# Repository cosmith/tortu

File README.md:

Tortu is an open source storyteller and music player for kids.

It's also a work in progress :)

Current state:

# Todo

## App
- [ ] interface to be able to quickly add a file from youtube/spotify
- [ ] use dall-e or equivalent api to generate cover pictures
- [ ] use any llm to generate a short name for the story
- [ ] use elevenlabs or equivalent api to generate name

## Tortu
- [x] read files from sd card
- [x] play sound
- [x] display something on the screen
- [ ] finalize design
- [x] implement music / story switch
- [x] add volume control
- [x] add 3.5mm jack output

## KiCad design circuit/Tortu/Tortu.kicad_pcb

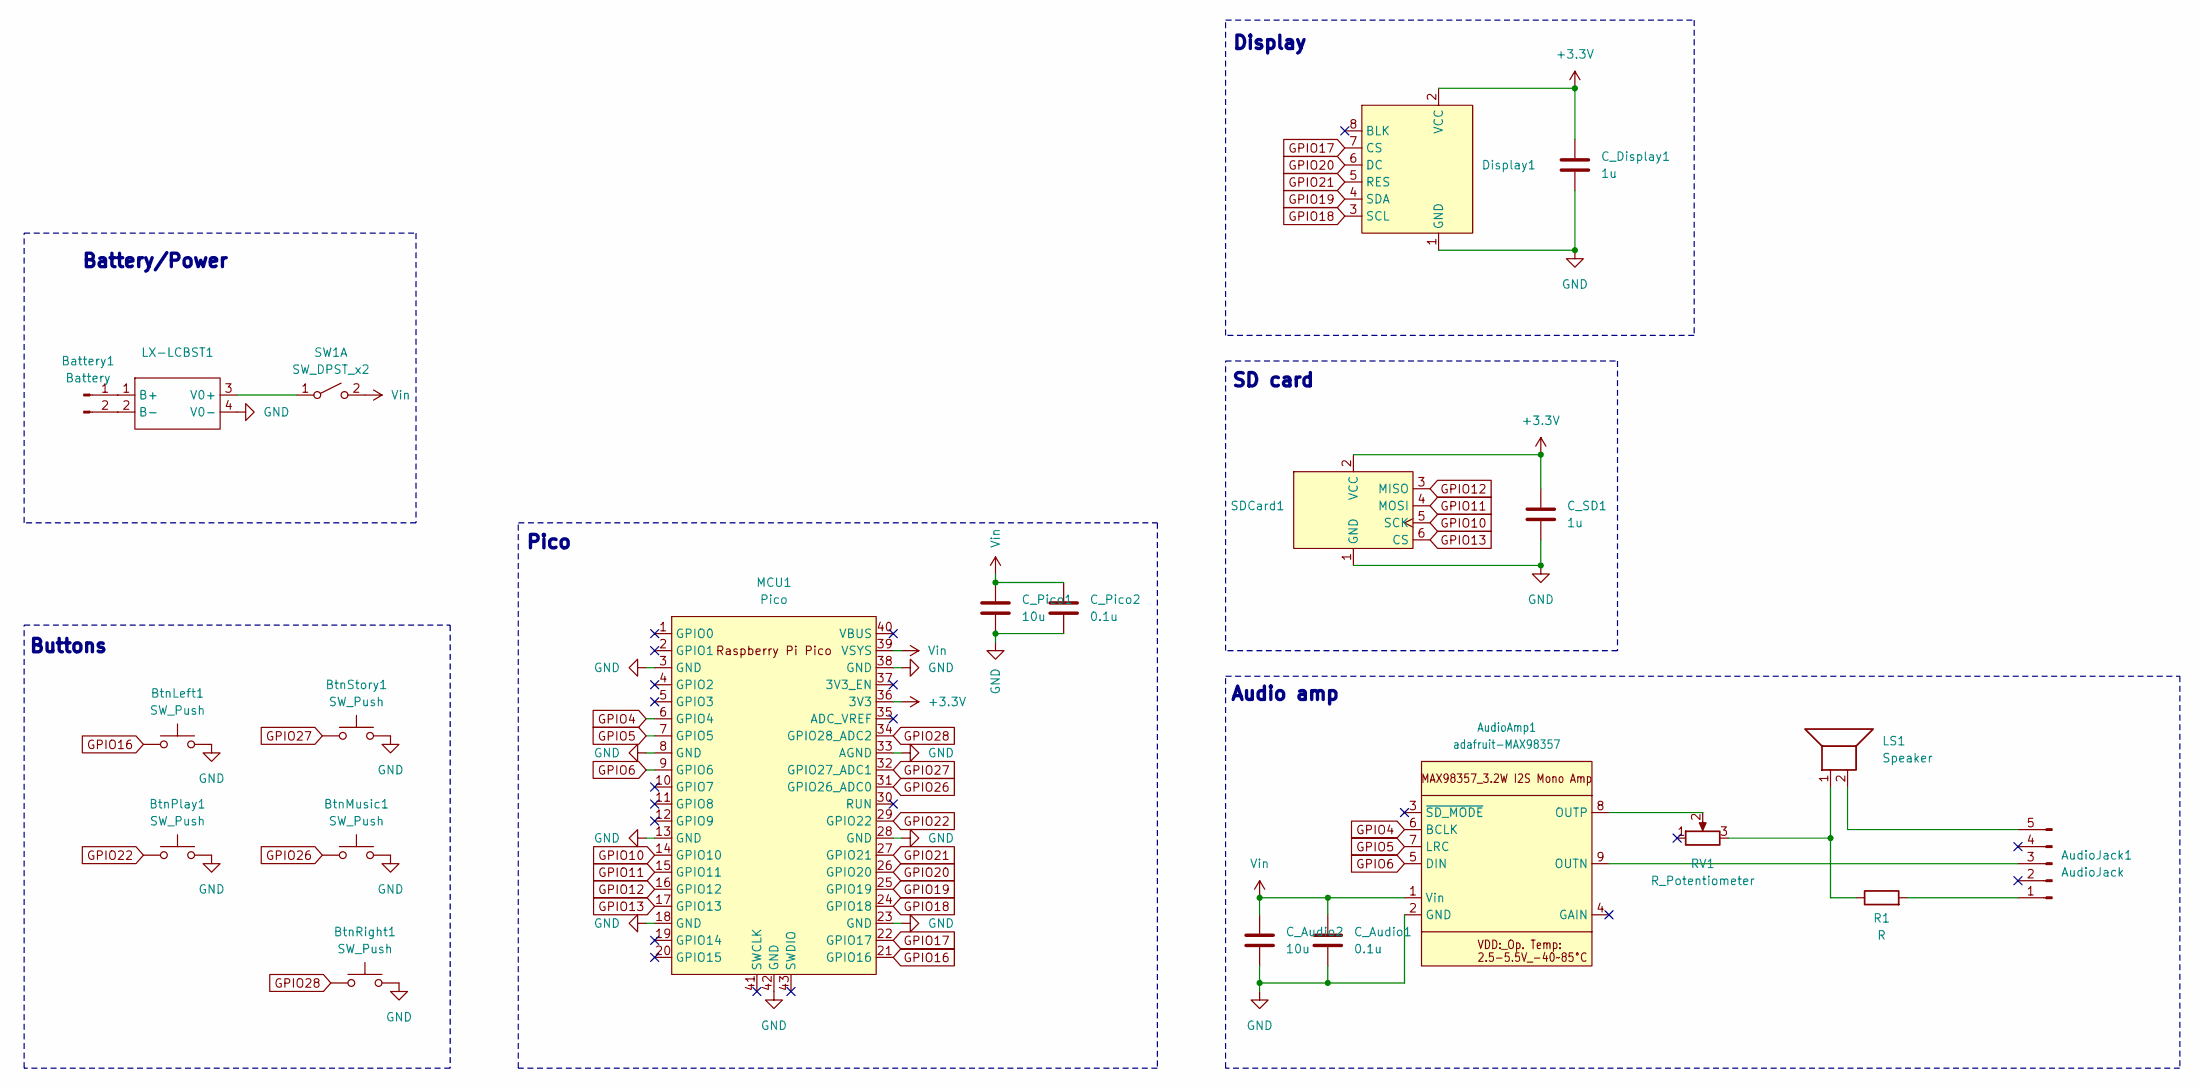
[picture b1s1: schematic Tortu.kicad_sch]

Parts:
AudioAmp1: adafruit-MAX98357
AudioJack1: AudioJack; PinHeader_1x05_P2.54mm_Vertical
Battery1: Battery; PinHeader_1x02_P2.54mm_Vertical
BtnLeft1: SW_Push; SW_PUSH_6mm_H5mm
BtnMusic1: SW_Push; SW_PUSH_6mm_H5mm
BtnPlay1: SW_Push; SW_PUSH_6mm_H5mm
BtnRight1: SW_Push; SW_PUSH_6mm_H5mm
BtnStory1: SW_Push; SW_PUSH_6mm_H5mm
C_Audio1: 0.1u; C_Disc_D3.8mm_W2.6mm_P2.50mm
C_Audio2: 10u; C_Disc_D3.8mm_W2.6mm_P2.50mm
C_Display1: 1u; C_Disc_D3.8mm_W2.6mm_P2.50mm
C_Pico1: 10u; C_Disc_D3.8mm_W2.6mm_P2.50mm
C_Pico2: 0.1u; C_Disc_D3.8mm_W2.6mm_P2.50mm
C_SD1: 1u; C_Disc_D3.8mm_W2.6mm_P2.50mm
Display1: Display_135x240IPS
LS1: Speaker; PinHeader_1x02_P2.54mm_Vertical
LX-LCBST1: BatteryCharginModule_LX-LCBST
MCU1: Pico; RPi_Pico_SMD_TH
R1: R; R_Axial_DIN0207_L6.3mm_D2.5mm_P10.16mm_Horizontal
RV1: R_Potentiometer; Potentiometer_Alps_RK163_Single_Horizontal
SDCard1: AZDelivery_SDCard
SW1: SW_DPST_x2; PinHeader_1x02_P2.54mm_Vertical

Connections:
+3.3V: C_Display1.1, C_SD1.1, Display1.2 (VCC), MCU1.36 (3V3), SDCard1.2 (VCC)
GND: AudioAmp1.2 (GND), BtnLeft1.2, BtnMusic1.2, BtnPlay1.2, BtnRight1.2, BtnStory1.2, C_Audio1.2, C_Audio2.2, C_Display1.2, C_Pico1.2, C_Pico2.2, C_SD1.2, Display1.1 (GND), LX-LCBST1.4 (V0-), MCU1.3 (GND), MCU1.8 (GND), MCU1.13 (GND), MCU1.18 (GND), MCU1.23 (GND), MCU1.28 (GND), MCU1.33 (AGND), MCU1.38 (GND), MCU1.42 (GND), SDCard1.1 (GND)
GPIO0: MCU1.1 (GPIO0)
GPIO1: MCU1.2 (GPIO1)
GPIO2: MCU1.4 (GPIO2)
GPIO4: AudioAmp1.6 (BCLK), MCU1.6 (GPIO4)
GPIO5: AudioAmp1.7 (LRC), MCU1.7 (GPIO5)
GPIO6: AudioAmp1.5 (DIN), MCU1.9 (GPIO6)
GPIO10: MCU1.14 (GPIO10), SDCard1.5 (SCK)
GPIO11: MCU1.15 (GPIO11), SDCard1.4 (MOSI)
GPIO12: MCU1.16 (GPIO12), SDCard1.3 (MISO)
GPIO13: MCU1.17 (GPIO13), SDCard1.6 (CS)
GPIO16: BtnLeft1.1, MCU1.21 (GPIO16)
GPIO17: Display1.7 (CS), MCU1.22 (GPIO17)
GPIO18: Display1.3 (SCL), MCU1.24 (GPIO18)
GPIO19: Display1.4 (SDA), MCU1.25 (GPIO19)
GPIO20: Display1.6 (DC), MCU1.26 (GPIO20)
GPIO21: Display1.5 (RES), MCU1.27 (GPIO21)
GPIO22: BtnPlay1.1, MCU1.29 (GPIO22)
GPIO26: BtnMusic1.1, MCU1.31 (GPIO26_ADC0)
GPIO27: BtnStory1.1, MCU1.32 (GPIO27_ADC1)
GPIO28: BtnRight1.1, MCU1.34 (GPIO28_ADC2)
unnamed: AudioAmp1.9 (OUTN), AudioJack1.3
unnamed: AudioAmp1.8 (OUTP), RV1.2
unnamed: AudioJack1.1, R1.2
unnamed: AudioJack1.5, LS1.2
unnamed: Battery1.1, LX-LCBST1.1 (B+)
unnamed: Battery1.2, LX-LCBST1.2 (B-)
unnamed: LS1.1, R1.1, RV1.3
unnamed: LX-LCBST1.3 (V0+), SW1.1 (A)
Vin: AudioAmp1.1 (Vin), C_Audio1.1, C_Audio2.1, C_Pico1.1, C_Pico2.1, MCU1.39 (VSYS), SW1.2 (B)

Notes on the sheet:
Buttons
Pico
Battery/Power
Display
Audio amp
SD card

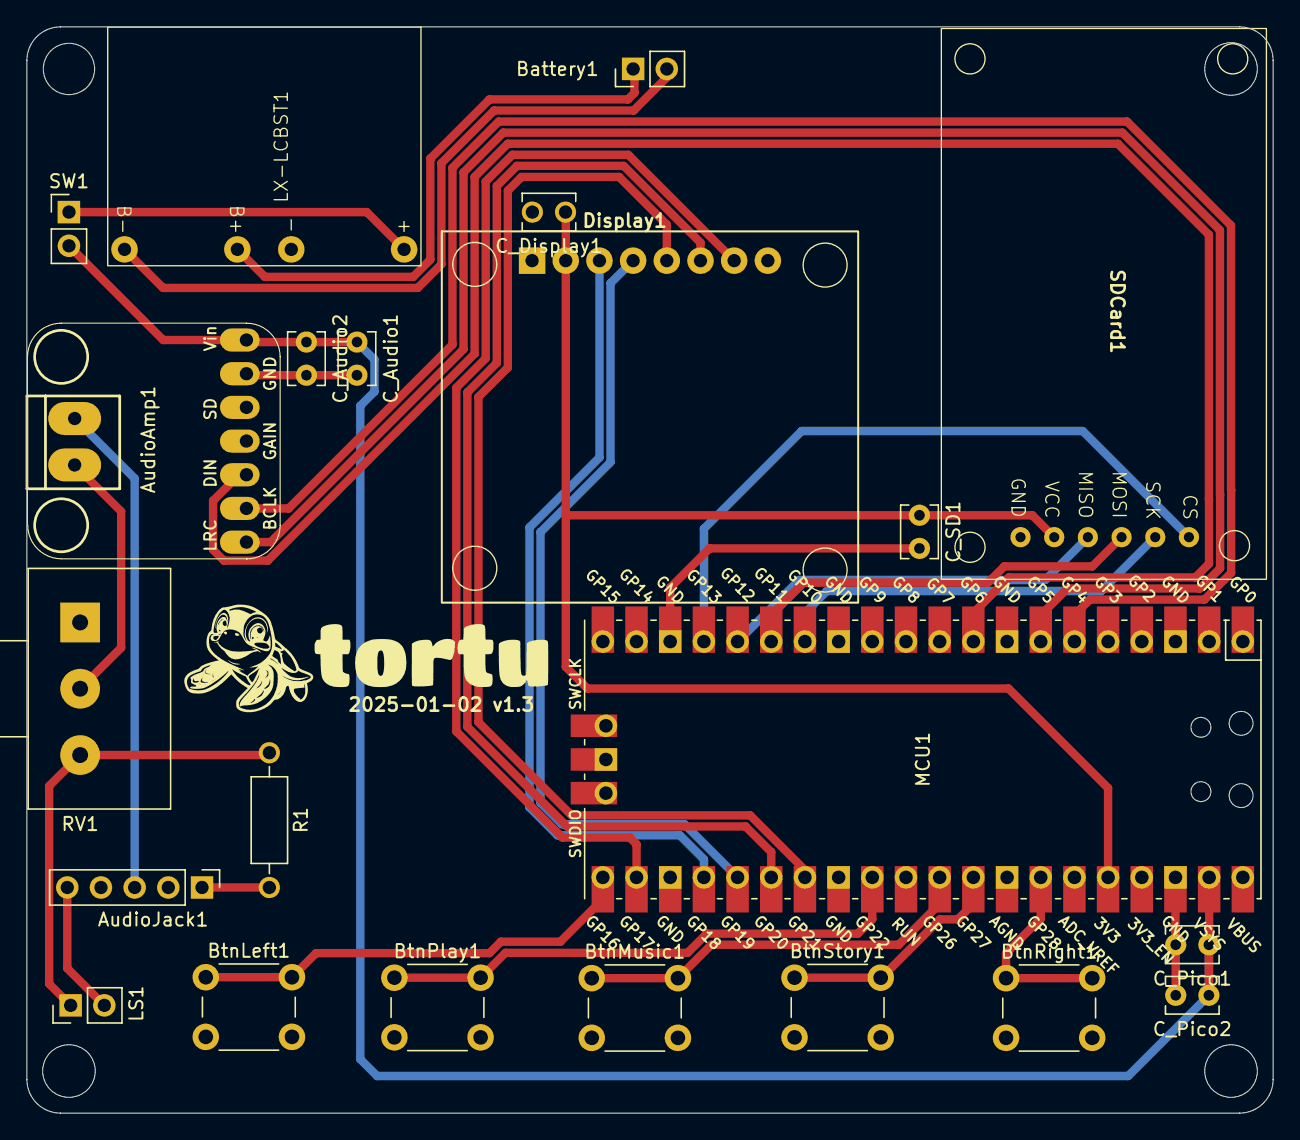
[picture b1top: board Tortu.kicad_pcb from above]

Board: 2 copper layers, 94.0 x 81.9 mm, 22 parts (0 on the bottom side), 28 nets.

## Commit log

2024-03-15 Download script
2024-03-15 readme
2024-03-15 Photo
2024-04-06 Move to Arduino / PlatformIO
2024-04-07 Splash
2024-05-04 Add buttons
2024-11-11 V1.1
2025-01-03 v1.3
2025-02-08 Some progress
